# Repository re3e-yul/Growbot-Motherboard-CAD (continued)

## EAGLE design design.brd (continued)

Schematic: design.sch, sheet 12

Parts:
C105: GRM033R60J104KE19D; 0201
R33: ERJ-1GEF1002C; 0201
R34: RC0201JR-070RL; 0201
RP1, RP2: DNP; RP741X083
U2: TS3A5223RSWR; UQFN-10

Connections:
15.UART1_RXD: RP1.1, U2.7 (NC2); also elsewhere on the board
15.UART1_TXD: RP1.2, U2.5 (NC1); also elsewhere on the board
15.UART2_RXD: RP2.4, U2.10 (NO2); also elsewhere on the board
15.UART2_TXD: RP2.3, U2.2 (NO1); also elsewhere on the board
15.VLOGIC_OUT_VLOGIC: R34.2; also elsewhere on the board
16.UART0_RXD: RP1.8, RP2.5, U2.9 (COM2); also elsewhere on the board
16.UART0_TXD: RP1.7, RP2.6, U2.3 (COM1); also elsewhere on the board
16.USB3_CC2_GPIO: R33.2, U2.4 (SEL1), U2.8 (SEL2); also elsewhere on the board
16.VLOGIC_VLOGIC: C105.1, R34.1, U2.1 (VCC); also elsewhere on the board
GND: C105.2, R33.1, U2.6 (GND); also elsewhere on the board

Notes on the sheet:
Quad 2 Input MUX

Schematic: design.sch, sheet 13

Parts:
J1, J2: DF40C-100DS-0.4V(51); HRS_DF40C-100DS-0.4V(51)
MP1, MP2, MP3, MP4: 9774015151R; WA-SMSI_9774___151
Q1: BSS138; SOT23
Q2, Q3: FDN360P; SOT23
R37: DNP; 0201
R38, R39, R44: RC0201JR-070RL; 0201
R40: ERJ-1GEF1002C; 0201

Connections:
1.8V_OUT$16: J1.88, J1.90, R37.1
2.5.0V_VCC_5.0: J1.77, J1.79, J1.81, J1.83, J1.85, J1.87; also elsewhere on the board
3.3V_OUT$16: J1.84, J1.86, Q2.3 (D), R39.1, R44.1
16.3.3V_VCC_3.3: Q3.3 (D), R38.2; also elsewhere on the board
16.GPIO2_GPIO: J1.58; also elsewhere on the board
16.GPIO3_GPIO: J1.56; also elsewhere on the board
16.GPIO4_GPIO: J1.54; also elsewhere on the board
16.GPIO5_GPIO: J1.34; also elsewhere on the board
16.GPIO6_GPIO: J1.30; also elsewhere on the board
16.GPIO7_GPIO: J1.37; also elsewhere on the board
16.GPIO8_GPIO: J1.39; also elsewhere on the board
16.GPIO9_GPIO: J1.40; also elsewhere on the board
16.GPIO10_GPIO: J1.44; also elsewhere on the board
16.GPIO11_GPIO: J1.38; also elsewhere on the board
16.GPIO12_GPIO: J1.31; also elsewhere on the board
16.GPIO13_GPIO: J1.28; also elsewhere on the board
16.GPIO16_GPIO: J1.29; also elsewhere on the board
16.GPIO17_GPIO: J1.50; also elsewhere on the board
16.GPIO18_GPIO: J1.49; also elsewhere on the board
16.GPIO19_GPIO: J1.26; also elsewhere on the board
16.GPIO20_GPIO: J1.27; also elsewhere on the board
16.GPIO21_GPIO: J1.25; also elsewhere on the board
16.GPIO22_GPIO: J1.46; also elsewhere on the board
16.GPIO23_GPIO: J1.47; also elsewhere on the board
16.GPIO24_GPIO: J1.45; also elsewhere on the board
16.GPIO25_GPIO: J1.41; also elsewhere on the board
16.GPIO26_GPIO: J1.24; also elsewhere on the board
16.GPIO27_GPIO: J1.48; also elsewhere on the board
16.HDMI0_CEC: J2.51; also elsewhere on the board
16.HDMI0_CLOCK_N: J2.90; also elsewhere on the board
16.HDMI0_CLOCK_P: J2.88; also elsewhere on the board
16.HDMI0_D0_N: J2.84; also elsewhere on the board
16.HDMI0_D0_P: J2.82; also elsewhere on the board
16.HDMI0_D1_N: J2.78; also elsewhere on the board
16.HDMI0_D1_P: J2.76; also elsewhere on the board
16.HDMI0_D2_N: J2.72; also elsewhere on the board
16.HDMI0_D2_P: J2.70; also elsewhere on the board
16.HDMI0_DDC_SCL: J2.100; also elsewhere on the board
16.HDMI0_DDC_SDA: J2.99; also elsewhere on the board
16.HDMI0_HPD: J2.53; also elsewhere on the board
16.PCIE_CLKREQ_GPIO: J2.2; also elsewhere on the board
16.PCIE_CLK_N: J2.12; also elsewhere on the board
16.PCIE_CLK_P: J2.10; also elsewhere on the board
16.PCIE_RST_GPIO: J2.9; also elsewhere on the board
16.PCIE_RX0_N: J2.18; also elsewhere on the board
16.PCIE_RX0_P: J2.16; also elsewhere on the board
16.PCIE_TX0_N: J2.24; also elsewhere on the board
16.PCIE_TX0_P: J2.22; also elsewhere on the board
16.SYS_EN_SYSEN: J1.100, Q1.1 (G), R40.2; also elsewhere on the board
16.UART0_RXD: J1.51; also elsewhere on the board
16.UART0_TXD: J1.55; also elsewhere on the board
16.USB3_CC1_GPIO: J1.94; also elsewhere on the board
16.USB3_CC2_GPIO: J1.96; also elsewhere on the board
16.USB_HOST_DRV_VBUS: R39.2; also elsewhere on the board
16.USB_HOST_D_N: J2.3; also elsewhere on the board
16.USB_HOST_D_P: J2.5; also elsewhere on the board
16.VLOGIC_VLOGIC: R38.1; also elsewhere on the board
16.nRESET_NRESET: J1.92; also elsewhere on the board
!RPIBOOT$16: J1.93; also elsewhere on the board
DS_LOAD$16: Q2.2 (S), Q3.2 (S)
EEPROM_!WP: J1.20
ETH_SYNC_IN: J1.16
ETH_SYNC_OUT: J1.18
GLOBAL_EN: J1.99
GND: J1.1, J1.2, J1.7, J1.8, J1.13, J1.14, J1.22, J1.23, J1.32, J1.33, J1.42, J1.43, J1.52, J1.53, J1.59, J1.60, J1.65, J1.66, J1.71, J1.74, J1.98, J2.7, J2.8, J2.13, J2.14, J2.19, J2.20, J2.25, J2.26, J2.31, J2.32, J2.37, J2.38, J2.44, J2.50, J2.55, J2.56, J2.61, J2.62, J2.67, J2.68, J2.73, J2.74, J2.79, J2.80, J2.85, J2.86, J2.91, J2.92, J2.97, J2.98, MP1.1, MP2.1, MP3.1, MP4.1, Q1.2 (S), R40.1; also elsewhere on the board
GPIO_VREF$16: J1.78, R37.2, R44.2; also elsewhere on the board
ID_SC$16: J1.35; also elsewhere on the board
ID_SD$16: J1.36; also elsewhere on the board
LOAD_GATE$16: Q1.3 (D), Q2.1 (G), Q3.1 (G)
PI_!LED_ACT: J1.21
PI_LED_!PWR: J1.95
SD_CLK: J1.57
SD_CMD: J1.62
SD_DAT0: J1.63
SD_DAT1: J1.67
SD_DAT2: J1.69
SD_DAT3: J1.61
SD_DAT4: J1.68
SD_DAT5: J1.64
SD_DAT6: J1.72
SD_DAT7: J1.70
SD_PWR_ON: J1.75
SD_VDD_OV: J1.73
VDAC_COMP: J2.11

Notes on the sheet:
Raspberry Pi CM4
GPIO
High Speed

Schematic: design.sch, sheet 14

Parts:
C109: GRM033R60J104KE19D; 0201
IC5: CAT24C256YI-GT3; TSSOP8
R10, R45: RC0201FR-071K5L; 0201
R11: ERJ-1GEF1002C; 0201
R41, R42, R43: CRCW0201100KFNED; 0201
S1: KMT021 NGJ LHS; KMT0

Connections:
!RPIBOOT$16: S1.3 (B), S1.4 (B'); also elsewhere on the board
A0$16: IC5.1 (A0), R43.2
A1$16: IC5.2 (A1), R42.2
A2$16: IC5.3 (A2), R41.2
GND: C109.2, IC5.4 (GND), IC5.7 (WP), R11.1, R41.1, R42.1; also elsewhere on the board
GPIO_VREF$16: C109.1, IC5.8 (VCC), R10.2, R43.1, R45.2; also elsewhere on the board
ID_SC$16: IC5.6 (SCL), R10.1; also elsewhere on the board
ID_SD$16: IC5.5 (SDA), R45.1; also elsewhere on the board
RPIBOOT_SWITCH$16: R11.2, S1.1 (A), S1.2 (A')

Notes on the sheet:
Raspberry Pi CM4

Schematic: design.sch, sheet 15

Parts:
U4: 67996-140HLF; 2X20

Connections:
2.5.0V_VCC_5.0: U4.2, U4.4; also elsewhere on the board
3.3.3V_VCC_3.3: U4.17; also elsewhere on the board
15.UART1_RXD: U4.10; also elsewhere on the board
15.UART1_TXD: U4.8; also elsewhere on the board
16.3.3V_VCC_3.3: U4.1; also elsewhere on the board
16.GPIO2_GPIO: U4.3; also elsewhere on the board
16.GPIO3_GPIO: U4.5; also elsewhere on the board
16.GPIO4_GPIO: U4.7; also elsewhere on the board
16.GPIO5_GPIO: U4.29; also elsewhere on the board
16.GPIO6_GPIO: U4.31; also elsewhere on the board
16.GPIO7_GPIO: U4.26; also elsewhere on the board
16.GPIO8_GPIO: U4.24; also elsewhere on the board
16.GPIO9_GPIO: U4.21; also elsewhere on the board
16.GPIO10_GPIO: U4.19; also elsewhere on the board
16.GPIO11_GPIO: U4.23; also elsewhere on the board
16.GPIO12_GPIO: U4.32; also elsewhere on the board
16.GPIO13_GPIO: U4.33; also elsewhere on the board
16.GPIO16_GPIO: U4.36; also elsewhere on the board
16.GPIO17_GPIO: U4.11; also elsewhere on the board
16.GPIO18_GPIO: U4.12; also elsewhere on the board
16.GPIO19_GPIO: U4.35; also elsewhere on the board
16.GPIO20_GPIO: U4.38; also elsewhere on the board
16.GPIO21_GPIO: U4.40; also elsewhere on the board
16.GPIO22_GPIO: U4.15; also elsewhere on the board
16.GPIO23_GPIO: U4.16; also elsewhere on the board
16.GPIO24_GPIO: U4.18; also elsewhere on the board
16.GPIO25_GPIO: U4.22; also elsewhere on the board
16.GPIO26_GPIO: U4.37; also elsewhere on the board
16.GPIO27_GPIO: U4.13; also elsewhere on the board
GND: U4.6, U4.9, U4.14, U4.20, U4.25, U4.30, U4.34, U4.39; also elsewhere on the board
P27: U4.27
P28: U4.28

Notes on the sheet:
40-Pin Header

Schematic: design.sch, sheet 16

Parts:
C112: GRM033R60J104KE19D; 0201
C113: C0603X5R1A103K030BA; 0201
C114: C1608X5R0J106M080AB; 0603
C115, C117: DNP; 1206
C116, C118: GRM31CR60J227ME11L; 1206
D1, D2, D5, D6: PS04LTVA1; D0402
D3, D4, D7: B72590D0050A060; D0402
FB1, FB2, FB3, FB4: BLM15PX121SN1D; 0402
K1: 61400826021
L3, L4: 7442335900; 0504-DLP11S
U8: TPS2052BDGNR; MSOP8-PAD

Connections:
2.5.0V_VCC_5.0: C112.1, FB2.1; also elsewhere on the board
21.USBH1_DRV_VBUS: U8.3 (EN1); also elsewhere on the board
21.USBH1_D_N: L3.2; also elsewhere on the board
21.USBH1_D_P: L3.3; also elsewhere on the board
21.USBH1_NOC: U8.8 (NOC1); also elsewhere on the board
21.USBH1_VBUS: D3.P2, FB4.2, U8.7 (OUT1)
21.USBH2_DRV_VBUS: U8.4 (EN2); also elsewhere on the board
21.USBH2_D_N: L4.2; also elsewhere on the board
21.USBH2_D_P: L4.3; also elsewhere on the board
21.USBH2_NOC: U8.5 (NOC2); also elsewhere on the board
21.USBH2_VBUS: D7.P2, FB3.2, U8.6 (OUT2)
A_GNDF$20: C113.1, D4.P2, FB1.2, K1.A4 (GND), K1.B4 (GND)
A_USB_D_N$20: D1.P2, K1.A2 (D-), L3.1
A_USB_D_P$20: D2.P2, K1.A3 (D+), L3.4
A_VBUS_$20: C115.1, C116.1, FB4.1, K1.A1 (VCC)
B_USB_D_N$20: D5.P2, K1.B2 (D-), L4.1
B_USB_D_P$20: D6.P2, K1.B3 (D+), L4.4
B_VBUS_$20: C117.1, C118.1, FB3.1, K1.B1 (VCC)
COMMON_SHIELD: D1.P1, D2.P1, D3.P1, D4.P1, D5.P1, D6.P1, D7.P1; also elsewhere on the board
GND: C112.2, C113.2, C114.2, C115.2, C116.2, C117.2, C118.2, FB1.1, K1.5 (SHIELD_A1), K1.6 (SHIELD_A2), K1.7 (SHIELD_B1), K1.8 (SHIELD_B2), U8.1 (GND), U8.TP (GND); also elsewhere on the board
VBUSF$20: C114.1, FB2.2, U8.2 (IN)

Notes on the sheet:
Dual Stacked USB Type A

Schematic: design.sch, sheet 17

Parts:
C1, C2, C3, C4, C5, C6, C7, C12, C14: GRM033R60J104KE19D; 0201
C8, C13, C15: GRM155R61A105KE15D; 0402
C9: CGB3B1X5R1A475K055AC; 0603
C10, C11: CC0201JRNPO9BN220; 0201
C16: DNP; 0402
IC1: DNP; SC70-5
R1: RMCF0201FT1M00; 0201
R2, R3, R5, R6, R7, R8: CRCW0201100KFNED; 0201
R4: RC0201FR-0712KL; 0201
R9: RC0201JR-070RL; 0201
U1: USB2513B-AEZC-TR; QFN36-6X6MM
Y1: 7M-24.000MAAJ-T; CRYSTAL-3225

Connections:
2.5.0V_VCC_5.0: C16.1, IC1.1 (OE), IC1.5 (VCC), R9.2; also elsewhere on the board
16.3.3V_VCC_3.3: C2.1, C3.1, C4.1, C5.1, C6.1, C7.1, C8.1, C9.1, R2.1, R3.2, U1.5 (VDD33), U1.10 (VDD33), U1.15 (VDD33), U1.23 (VDD33), U1.29 (VDD33), U1.36 (VDD33); also elsewhere on the board
16.USB_HOST_DRV_VBUS: IC1.2 (I); also elsewhere on the board
16.USB_HOST_D_N: U1.30 (USBDM_UP); also elsewhere on the board
16.USB_HOST_D_P: U1.31 (USBDP_UP); also elsewhere on the board
16.USB_HOST_VBUS: IC1.4 (O), R9.1
21.USBH1_DRV_VBUS: U1.12 (PRTPWR1); also elsewhere on the board
21.USBH1_D_N: U1.1 (USBDM_DN1); also elsewhere on the board
21.USBH1_D_P: U1.2 (USBDP_DN1); also elsewhere on the board
21.USBH1_NOC: U1.13 (OCS_N1); also elsewhere on the board
21.USBH2_DRV_VBUS: U1.16 (PRTPWR2); also elsewhere on the board
21.USBH2_D_N: U1.3 (USBDM_DN2); also elsewhere on the board
21.USBH2_D_P: U1.4 (USBDP_DN2); also elsewhere on the board
21.USBH2_NOC: U1.17 (OCS_N2); also elsewhere on the board
GND: C1.2, C2.2, C3.2, C4.2, C5.2, C6.2, C7.2, C8.2, C9.2, C10.2, C11.2, C12.2, C13.2, C14.2, C15.2, C16.2, IC1.3 (GND), R4.1, R5.1, R6.1, R7.1, R8.1, U1.EPAD (VSS), U1.EXP1 (VSS), U1.EXP2 (VSS), U1.EXP3 (VSS), U1.EXP4 (VSS), U1.EXP5 (VSS), U1.EXP6 (VSS), U1.EXP7 (VSS), U1.EXP8 (VSS), Y1.2, Y1.4; also elsewhere on the board
USB_CRFILT$21: C13.1, C14.1, U1.14 (CRFILT)
USB_HS_IND$21: R6.2, U1.25 (HS_IND/CFG_SEL1)
USB_NRESET$21: C12.1, R3.1, U1.26 (RESET_N)
USB_PLLFILT$21: C1.1, C15.1, U1.34 (PLLFILT)
USB_RBIAS$21: R4.2, U1.35 (RBIAS)
USB_SCL$21: R5.2, U1.24 (SCL/CFG_SEL0)
USB_SDA$21: R8.2, U1.22 (SDA/NON_REM1)
USB_SUSP_IND$21: R7.2, U1.28 (SUSP_IND/NON_REM0)
USB_VBUS_DET$21: R2.2, U1.27 (VBUS_DET)
USB_XTAL1$21: C11.1, R1.2, U1.33 (XTALIN), Y1.3
USB_XTAL2$21: C10.1, R1.1, U1.32 (XTALOUT), Y1.1

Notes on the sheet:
USB Hub

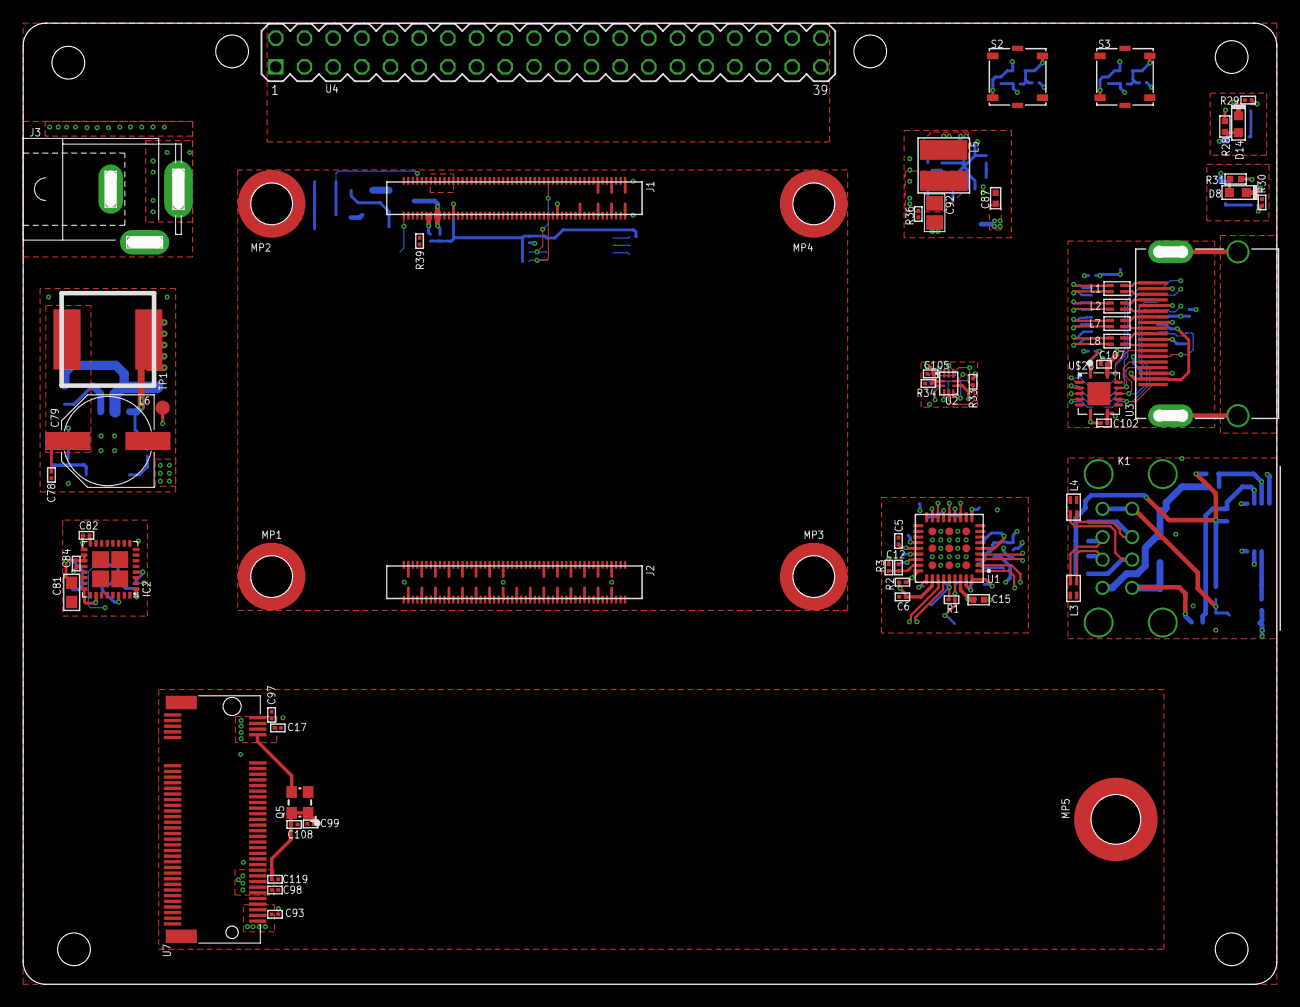
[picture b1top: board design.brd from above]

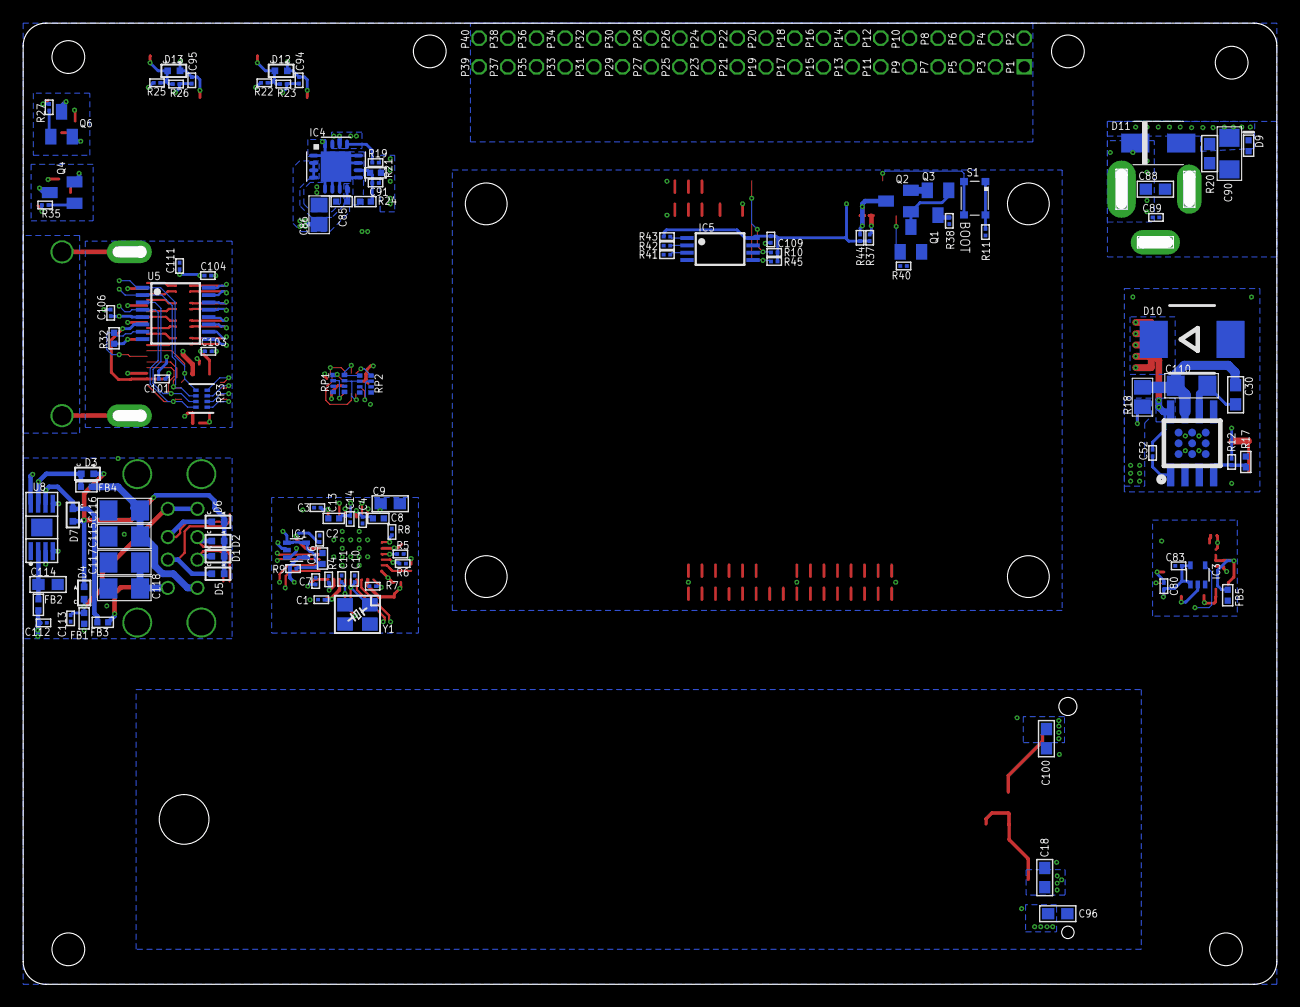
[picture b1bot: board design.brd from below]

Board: 6 copper layers, 111.0 x 85.1 mm, 173 parts (105 on the bottom side), 140 nets.

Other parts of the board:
U$12, U$14, U$16, U$18, U$30, U$32: DNP; GEPPETTO_HOLE_2.9
